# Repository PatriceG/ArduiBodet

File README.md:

# ArduiBodet	
Horloge mère pour Horloge de type *Bodet 1/2 Minute* pilotée par Arduino

Ce code nécessite les librairies suivantes:
  -DS3231 : [http://m5.img.dxcdn.com/CDDriver/CD/sku.222910.rar](http://m5.img.dxcdn.com/CDDriver/CD/sku.222910.rar)
  -Low-Power: [https://github.com/rocketscream/Low-Power] (https://github.com/rocketscream/Low-Power)
  
L'IDE utilisé est **AtmelStudio + VisualMicro** mais le code est compatible avec l'IDE Arduino.

Les détails de la construction de l'horloge mère sont donnés ici: [http://breizhmakers.over-blog.com/tag/horlogebodet/](http://breizhmakers.over-blog.com/tag/horlogebodet/)

# Les objectifs fixés sont: 

- Faible coût
- Alimentation 9V (nécessaire pour piloter l'horloge)
- Application automatique des changements d'heure.
- Très bonne stabilité de l'horloge (2 ppm soit environ 1 minute/an)
- Interrupteur Marche/Arrêt
- Interrupteur de mise en mode avance rapide pour mise à l'heure.

# Comment Flasher le Firmware

La plupart des ATMega328 sont livrés configurés pour fonctionner avec un quartz externe à 16MHz.

Avant de pouvoir flasher le firmware il faut donc installer l'ATMega sur une Breadboard en y câblant un quartz 16MHz et ses condensateurs associés, et y brancher le programmateur (j'utilise un USBAsp).

J'ai ensuite suivi [cette doc](https://www.electrosoftcloud.com/en/changing-the-arduino-clock-speed/) avec un IDE Arduino 1.8.18, mais cela fonctionne aussi avec l'IDE Arduino 2.x, pour configurer l'Arduino en mode horloge interne 1MHz (ou 8MHz, ça fonctionne aussi).

Une fois les définitions de Board MiniCore installées et choisi ATMega328 on a accès à tout un tas de settings, dont le mode de fonctionnement de l'horloge. 
Il reste ensuite à cliquer sur "Graver la séquence d'initialisation" pour flasher cette config de fuses (avec le programmateur choisi. J'utilise un USBAsp).

Il est ensuite conseillé de flasher le sketch Blink et de vérifier que la pin correspondant à D13 clignotte bien à 1 Hz

On peut alors flasher le sketch de l'Horloge.

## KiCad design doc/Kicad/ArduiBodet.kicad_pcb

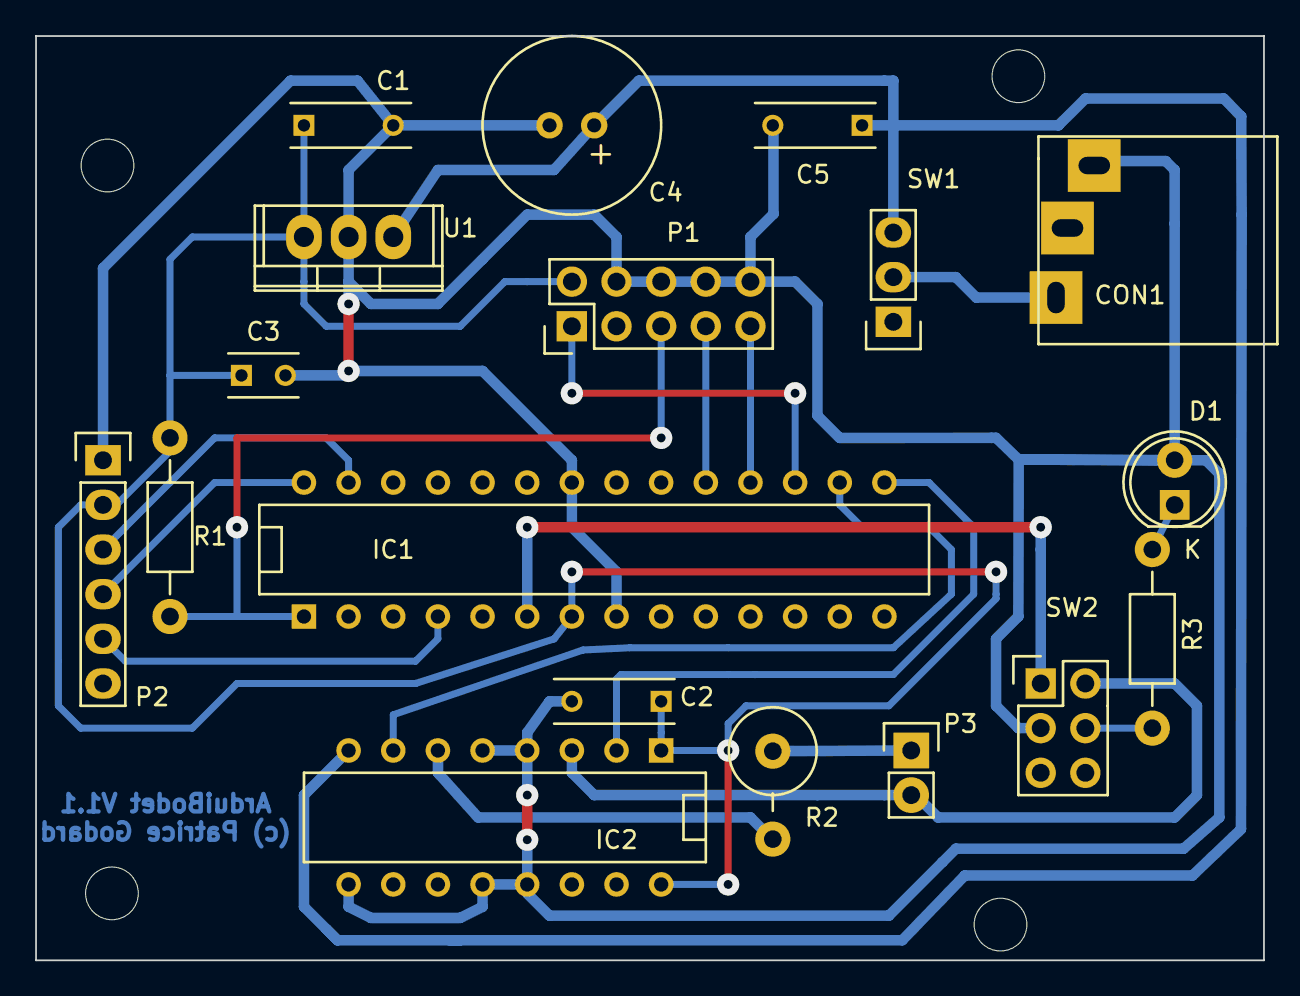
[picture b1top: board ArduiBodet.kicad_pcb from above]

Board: 2 copper layers, 69.8 x 52.6 mm, 18 parts (0 on the bottom side), 19 nets.

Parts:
C1: 100nF; C_Rect_L7_W2.5_P2.5
C2: 100 nF; C_Rect_L7_W2.5_P2.5
C3: 100nF; C_Rect_L4_W2.5_P2.5
C4: 1000 uF; Elko_vert_20x10mm_RM2.5
C5: 330nF; C_Rect_L7_W2.5_P2.5
CON1: BARREL_JACK; BARREL_JACK_FR
D1: LED; LED-5MM
IC1: ATMEGA328-P; DIP-28__300
IC2: SN754410; DIP-16__300
P1: ICSP_10_PIN; Pin_Header_Straight_2x05
P2: DS3231_Breakout_Connector; Pin_Header_Straight_1x06
P3: Moteur Horloge; Pin_Header_Straight_1x02
R1: 22K; Resistor_Horizontal_RM10mm
R2: 47; Resistor_Vertical_RM5mm
R3: 470; Resistor_Horizontal_RM10mm
SW1: SWITCH_INV; Pin_Header_Straight_1x03
SW2: Switch_DPST; Pin_Header_Straight_2x03_for_SPDT_switch
U1: LM7805CT; TO-220

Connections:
GNDA: C1.2, C2.2, C3.2, C4.2, C5.2, CON1.2, D1.2, IC1.8, IC1.22, IC2.4, IC2.5, IC2.9, IC2.12, IC2.13, P1.4, P1.6, P1.8, P1.10, P2.1, SW2.2, U1.2
unnamed: C1.1, C2.1, C3.1, IC1.7, IC2.1, IC2.16, P1.2, P2.2, R1.1, U1.3
unnamed: C4.1, C5.1, IC2.8, SW1.3, U1.1
unnamed: CON1.1, SW1.2
unnamed: D1.1, R3.1
unnamed: IC1.1, P1.5, R1.2
unnamed: IC1.4, P2.5
unnamed: IC1.6, SW2.1
unnamed: IC1.15, IC2.2
unnamed: IC1.16, IC2.7
unnamed: IC1.17, P1.1
unnamed: IC1.18, P1.9
unnamed: IC1.19, P1.7
unnamed: IC1.27, P2.3
unnamed: IC1.28, P2.4
unnamed: IC2.3, P3.2, SW2.3
unnamed: IC2.6, R2.2
unnamed: P3.1, R2.1
unnamed: R3.2, SW2.4

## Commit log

2015-04-26 Initial Commit - working Proof of Concept
2015-04-26 changed blog URL to point to a category
2015-05-01 added schematics (work-in-progress)
2015-05-01 added a copy of the LowPower library for future reference
2015-05-01 DS3231, driving by external interrupts & DST changes seem OK on an Arduino Uno (ATMega 328)
2015-05-01 fixed signed declaration
2015-05-03 reset pulse width to 400ms.
2015-05-04 routing in progress
2015-05-05 updated to changed goals
2015-05-05 DST change tests
2015-05-07 fully routed #1 fixed custom BARREL_JACK_FR.kicad_mod
2015-05-08 routing almost done
2015-05-10 routing done. needs proof-checking
2015-05-20 don't remember :)
2015-05-25 typon terminé et vérifié correction empreinte BARREL_JACK_FR
2015-05-25 fix BARREL_JACK_FR.kicad_mod
2015-05-27 typon final
2015-11-02 Version 1.1. Typon amélioré (pads condos plus larges, espacements,...
2025-05-21 ajout d'une doc expliquant comment flasher le firmware et passer l'ATMega en mode horloge interne
2025-05-21 ajout mention que ça fonctionne aussi avec l'IDE Arduino 2.x
